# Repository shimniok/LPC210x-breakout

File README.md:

Eagle CAD files for NXP LPC2101, LPC2102, LPC2103 ARM7 Breakout Board

# Features
* Compact 36-DIP package for breadboard prototyping
* Uses standard FTDI 6-pin header for programming
* Program switch makes it easy to flash new programs
* 800mA 3.3V onboard regulator to power MCU and projects
* Onboard 1.8V regulator
* Three power options: FTDI, VIN pin, or external 3.3V supply
* Reset switch
* Debug jumper
* Pin 0.14 is exposed for automatic program mode with RTS

# Files
* ```examples/``` - Example LPC2103 C Programs
* ```documentation/``` - Pinout diagram

datasheet [[pdf](http://www.nxp.com/documents/data_sheet/LPC2101_02_03.pdf)]

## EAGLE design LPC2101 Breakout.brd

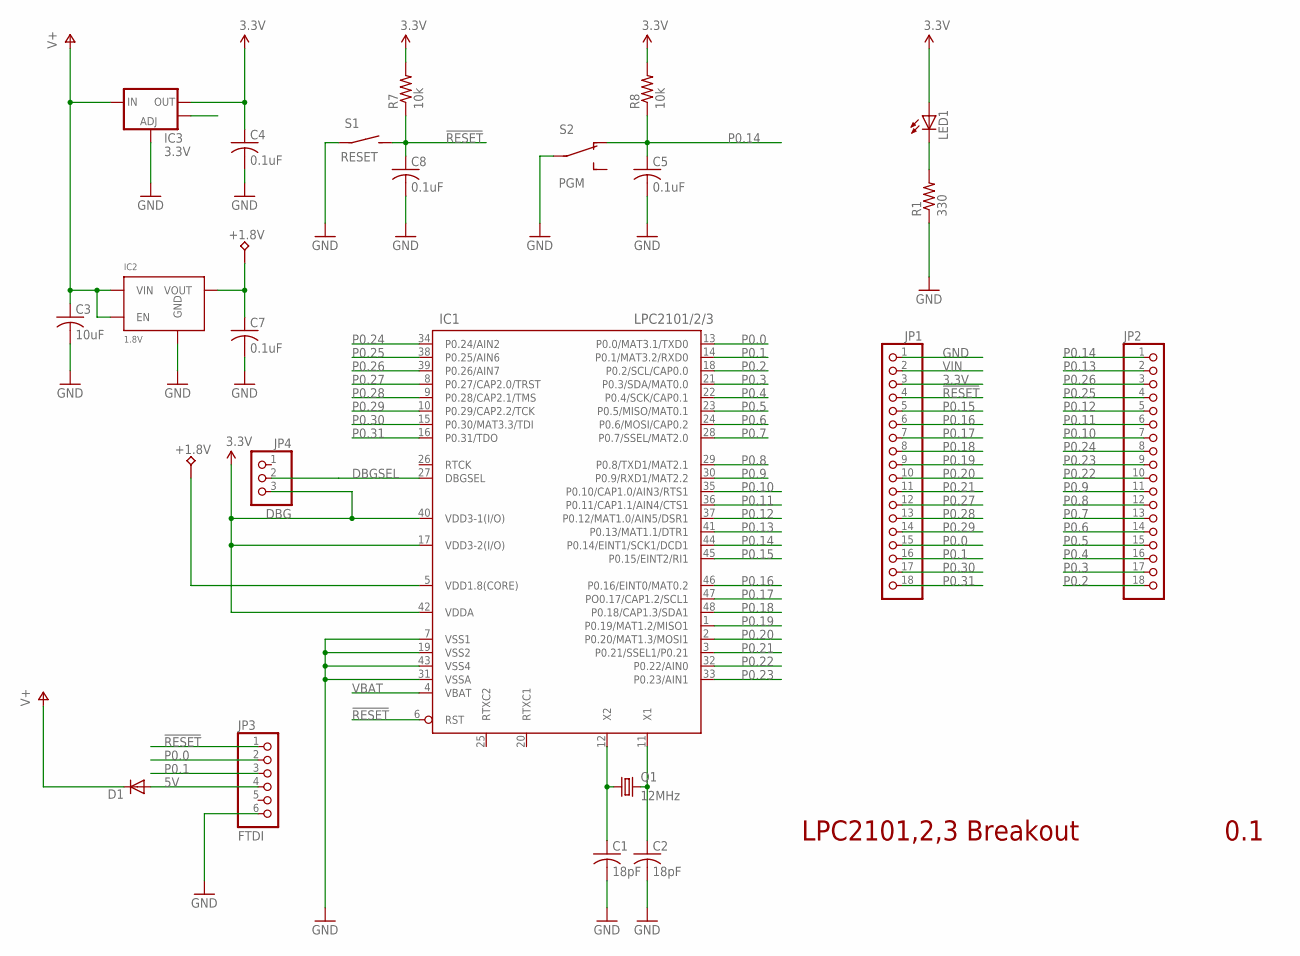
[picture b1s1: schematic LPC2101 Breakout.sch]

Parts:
C1, C2: 18pF; C0603; PARTNO C1608C0G1H180J
C3: 10uF; C0603; PARTNO C1608X5R0J106M_DK
C4, C5, C7, C8: 0.1uF; C0603; PARTNO CX0603MRX7R6BB104
D1: DIODE-SOD123; SOD123; PARTNO CGRM4001-G
IC1: LPC2101/2/3; LQFP48; PARTNO LPC2101FBD48,151
IC2: 1.8V; SOT23-5; PARTNO TLV70018DDCT
IC3: 3.3V; SOT223; PARTNO SALVAGE
JP1, JP2: PINHD-1X18_2.54-S; 1X18-S
JP3: FTDI; 1X06-S
JP4: DBG; 1X03M; PARTNO 951103-8622-AR
LED1: LEDCHIPLED_1206; CHIPLED_1206; PARTNO LG N971-KN-1
Q1: 12MHz; TC26H; PARTNO CSA309-12.000MABJ-UB
R1: 330; R0603; PARTNO ERJ-3GEYJ331V
R7, R8: 10k; R0603; PARTNO ERJ-3GEYJ103V
S1: RESET; 6MMTACTILE; PARTNO SALVAGE
S2: PGM; OS102011MA1Q; PARTNO OS102011MA1QS1

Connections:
3.3V: C4.1, IC1.17 (VDD3-2(I/O)), IC1.40 (VDD3-1(I/O)), IC1.42 (VDDA), IC3.2 (OUT), JP1.3, JP4.3, LED1.A, R7.2, R8.2
5V: D1.A, JP3.4
!RESET: C8.1, IC1.6 (RST), JP1.4, JP3.1, R7.1, S1.P$2 (S)
+1.8V: C7.1, IC1.5 (VDD1.8(CORE)), IC2.5 (VOUT)
DBGSEL: IC1.27 (DBGSEL), JP4.2
GND: C1.2, C2.2, C3.2, C4.2, C5.2, C7.2, C8.2, IC1.7 (VSS1), IC1.19 (VSS2), IC1.31 (VSSA), IC1.43 (VSS4), IC2.2 (GND), IC3.1 (ADJ), JP1.1, JP3.6, R1.1, S1.P$1, S2.P$2
HS1: IC3.4 (OUT)
unnamed: LED1.C, R1.2
unnamed: C2.1, IC1.11 (X1), Q1.2
unnamed: C1.1, IC1.12 (X2), Q1.1
P0.0: IC1.13 (P0.0/MAT3.1/TXD0), JP1.15, JP3.2
P0.1: IC1.14 (P0.1/MAT3.2/RXD0), JP1.16, JP3.3
P0.2: IC1.18 (P0.2/SCL/CAP0.0), JP2.18
P0.3: IC1.21 (P0.3/SDA/MAT0.0), JP2.17
P0.4: IC1.22 (P0.4/SCK/CAP0.1), JP2.16
P0.5: IC1.23 (P0.5/MISO/MAT0.1), JP2.15
P0.6: IC1.24 (P0.6/MOSI/CAP0.2), JP2.14
P0.7: IC1.28 (P0.7/SSEL/MAT2.0), JP2.13
P0.8: IC1.29 (P0.8/TXD1/MAT2.1), JP2.12
P0.9: IC1.30 (P0.9/RXD1/MAT2.2), JP2.11
P0.10: IC1.35 (P0.10/CAP1.0/AIN3/RTS1), JP2.7
P0.11: IC1.36 (P0.11/CAP1.1/AIN4/CTS1), JP2.6
P0.12: IC1.37 (P0.12/MAT1.0/AIN5/DSR1), JP2.5
P0.13: IC1.41 (P0.13/MAT1.1/DTR1), JP2.2
P0.14: C5.1, IC1.44 (P0.14/EINT1/SCK1/DCD1), JP2.1, R8.1, S2.P$1 (O1)
P0.15: IC1.45 (P0.15/EINT2/RI1), JP1.5
P0.16: IC1.46 (P0.16/EINT0/MAT0.2), JP1.6
P0.17: IC1.47 (PO0.17/CAP1.2/SCL1), JP1.7
P0.18: IC1.48 (P0.18/CAP1.3/SDA1), JP1.8
P0.19: IC1.1 (P0.19/MAT1.2/MISO1), JP1.9
P0.20: IC1.2 (P0.20/MAT1.3/MOSI1), JP1.10
P0.21: IC1.3 (P0.21/SSEL1/P0.21), JP1.11
P0.22: IC1.32 (P0.22/AIN0), JP2.10
P0.23: IC1.33 (P0.23/AIN1), JP2.9
P0.24: IC1.34 (P0.24/AIN2), JP2.8
P0.25: IC1.38 (P0.25/AIN6), JP2.4
P0.26: IC1.39 (P0.26/AIN7), JP2.3
P0.27: IC1.8 (P0.27/CAP2.0/TRST), JP1.12
P0.28: IC1.9 (P0.28/CAP2.1/TMS), JP1.13
P0.29: IC1.10 (P0.29/CAP2.2/TCK), JP1.14
P0.30: IC1.15 (P0.30/MAT3.3/TDI), JP1.17
P0.31: IC1.16 (P0.31/TDO), JP1.18
VBAT: IC1.4 (VBAT)
VIN: C3.1, D1.C, IC2.1 (VIN), IC2.3 (EN), IC3.3 (IN), JP1.2

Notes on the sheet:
LPC2101,2,3 Breakout
0.1

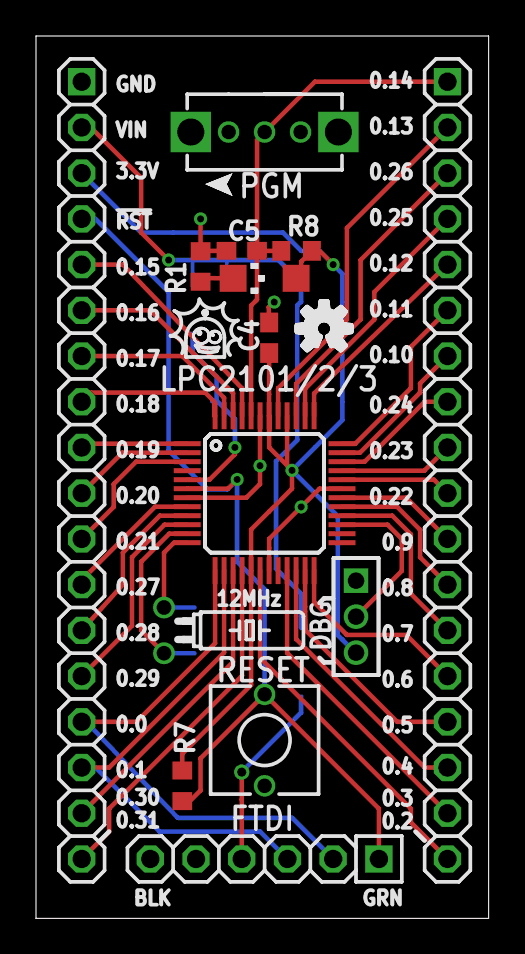
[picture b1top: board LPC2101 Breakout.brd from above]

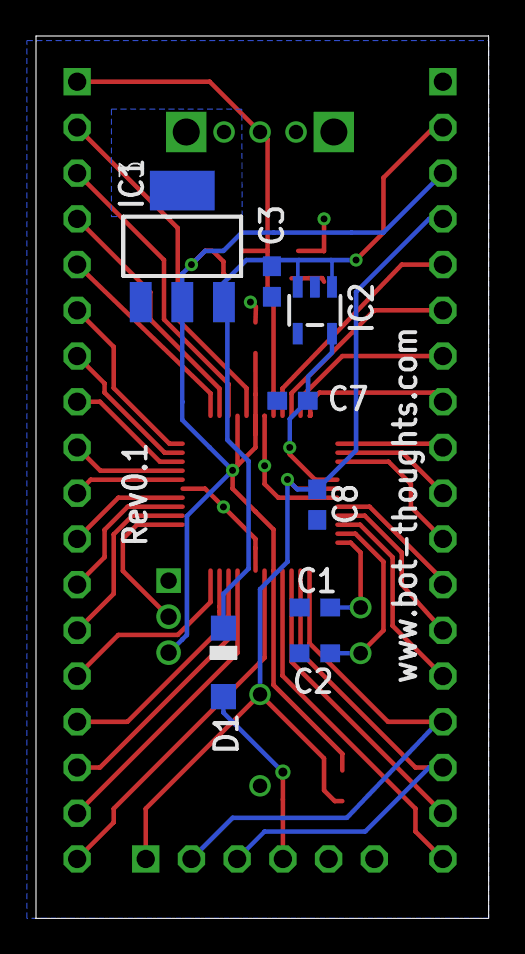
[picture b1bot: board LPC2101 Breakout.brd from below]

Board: 2 copper layers, 25.1 x 49.0 mm, 22 parts (8 on the bottom side), 42 nets.

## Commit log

2012-02-23 Initial directory structure.
2012-02-23 Initial Revision 0.1
2012-02-23 Revision 0.1 of LPC210x breakout
2012-02-23 Tag Rev 0.1
2012-02-23 Moving to folder
2012-02-24 Initial Pinout diagram
2012-02-24 Initial pinout
2012-02-24 Cropped image
2012-02-27 Initial Revision
2012-02-27 Not source code
2012-02-27 Updated project configurations
2012-02-27 Revised readme
2012-02-27 Minor updates
2012-02-27 Updated code for simple glow on glow off.
2012-02-27 Put readme material in main.c
2012-02-27 Updated documentation
2012-02-27 Revised comments/documentation
2012-02-27 Moved documentation into main.c
2012-02-27 Restoring files from tag
2012-02-27 Adding Rev0.1 Examples
2012-04-03 Initial revision of timer/interrupt-based LED blink
2015-05-04 Migrating wiki contents from Google Code
2015-08-07 Moved all files into top level directory
2015-08-07 Moved electronics to subdir, moved documentation to subdir
2015-08-07 Added readme
